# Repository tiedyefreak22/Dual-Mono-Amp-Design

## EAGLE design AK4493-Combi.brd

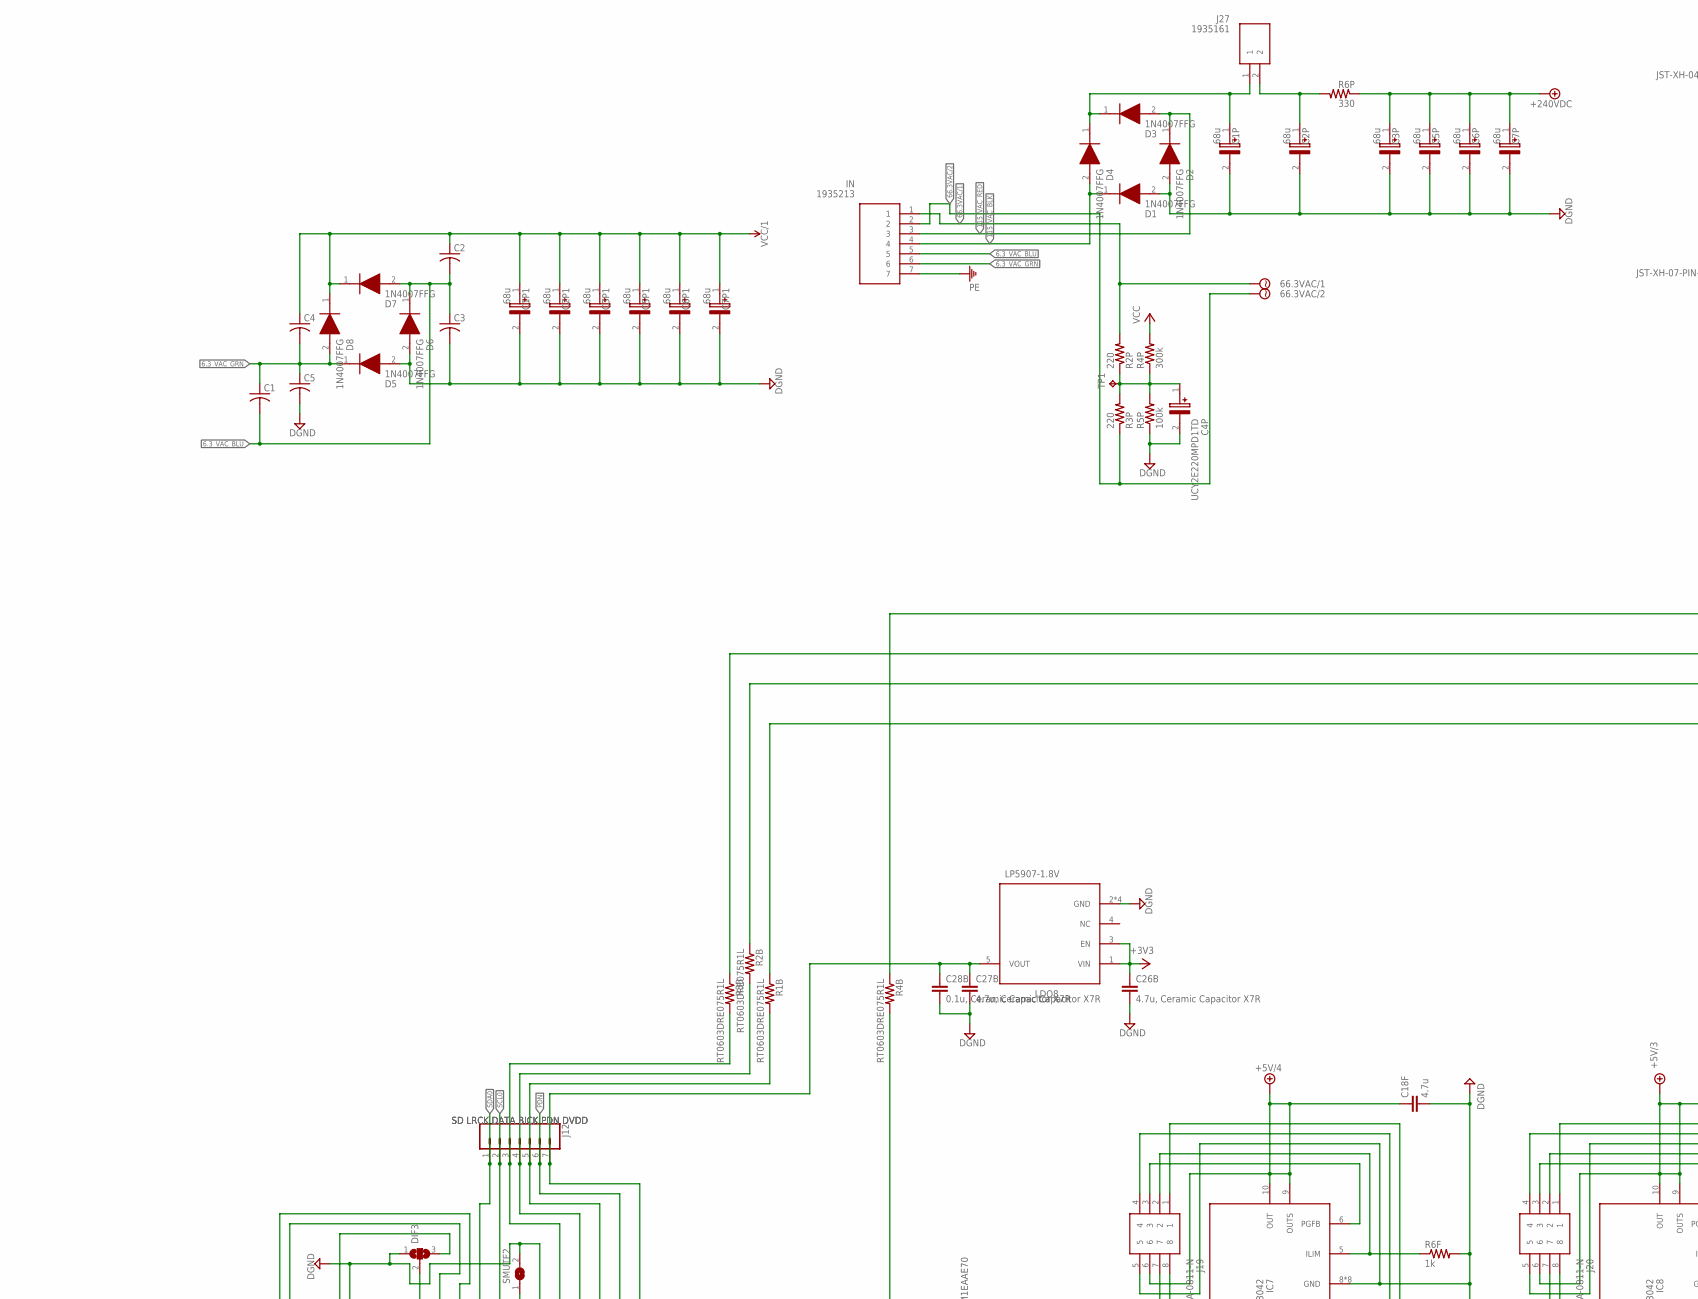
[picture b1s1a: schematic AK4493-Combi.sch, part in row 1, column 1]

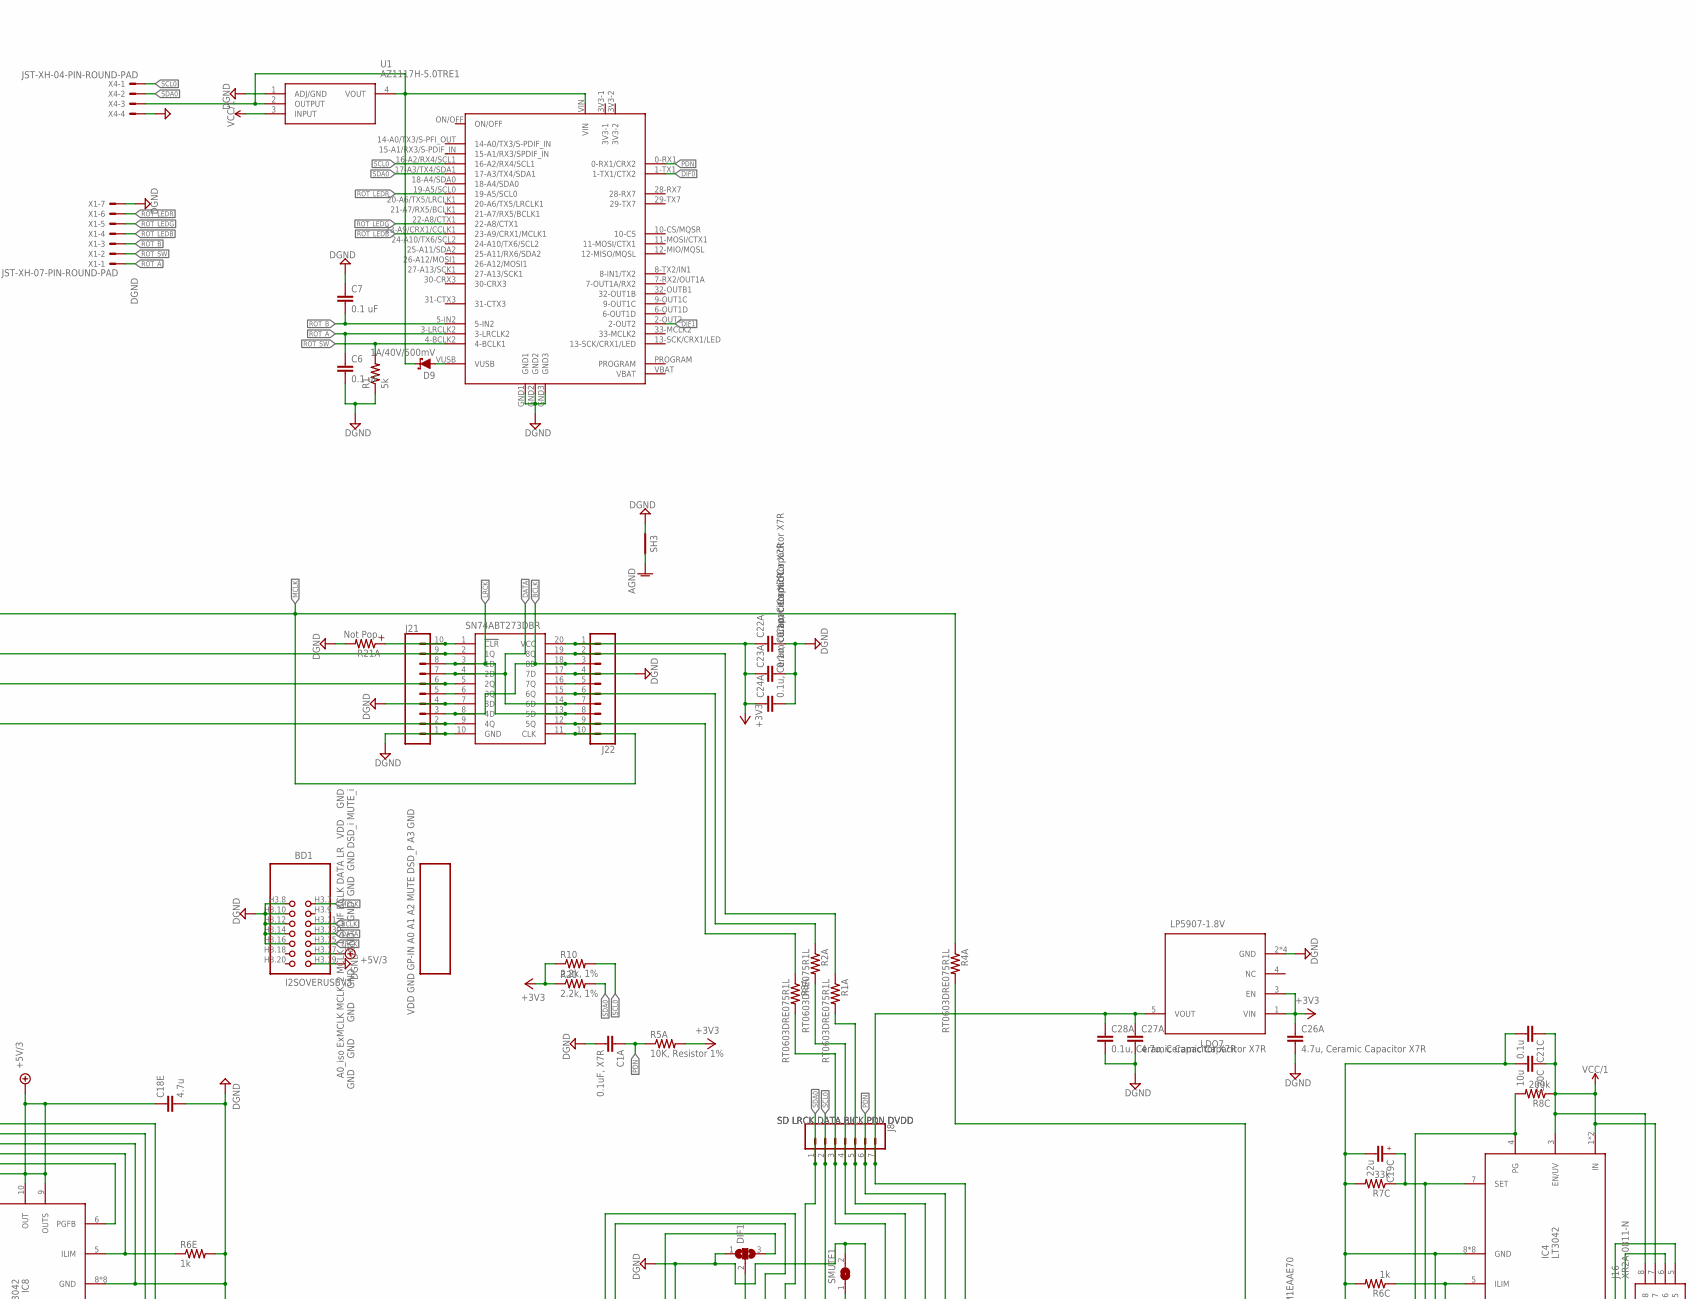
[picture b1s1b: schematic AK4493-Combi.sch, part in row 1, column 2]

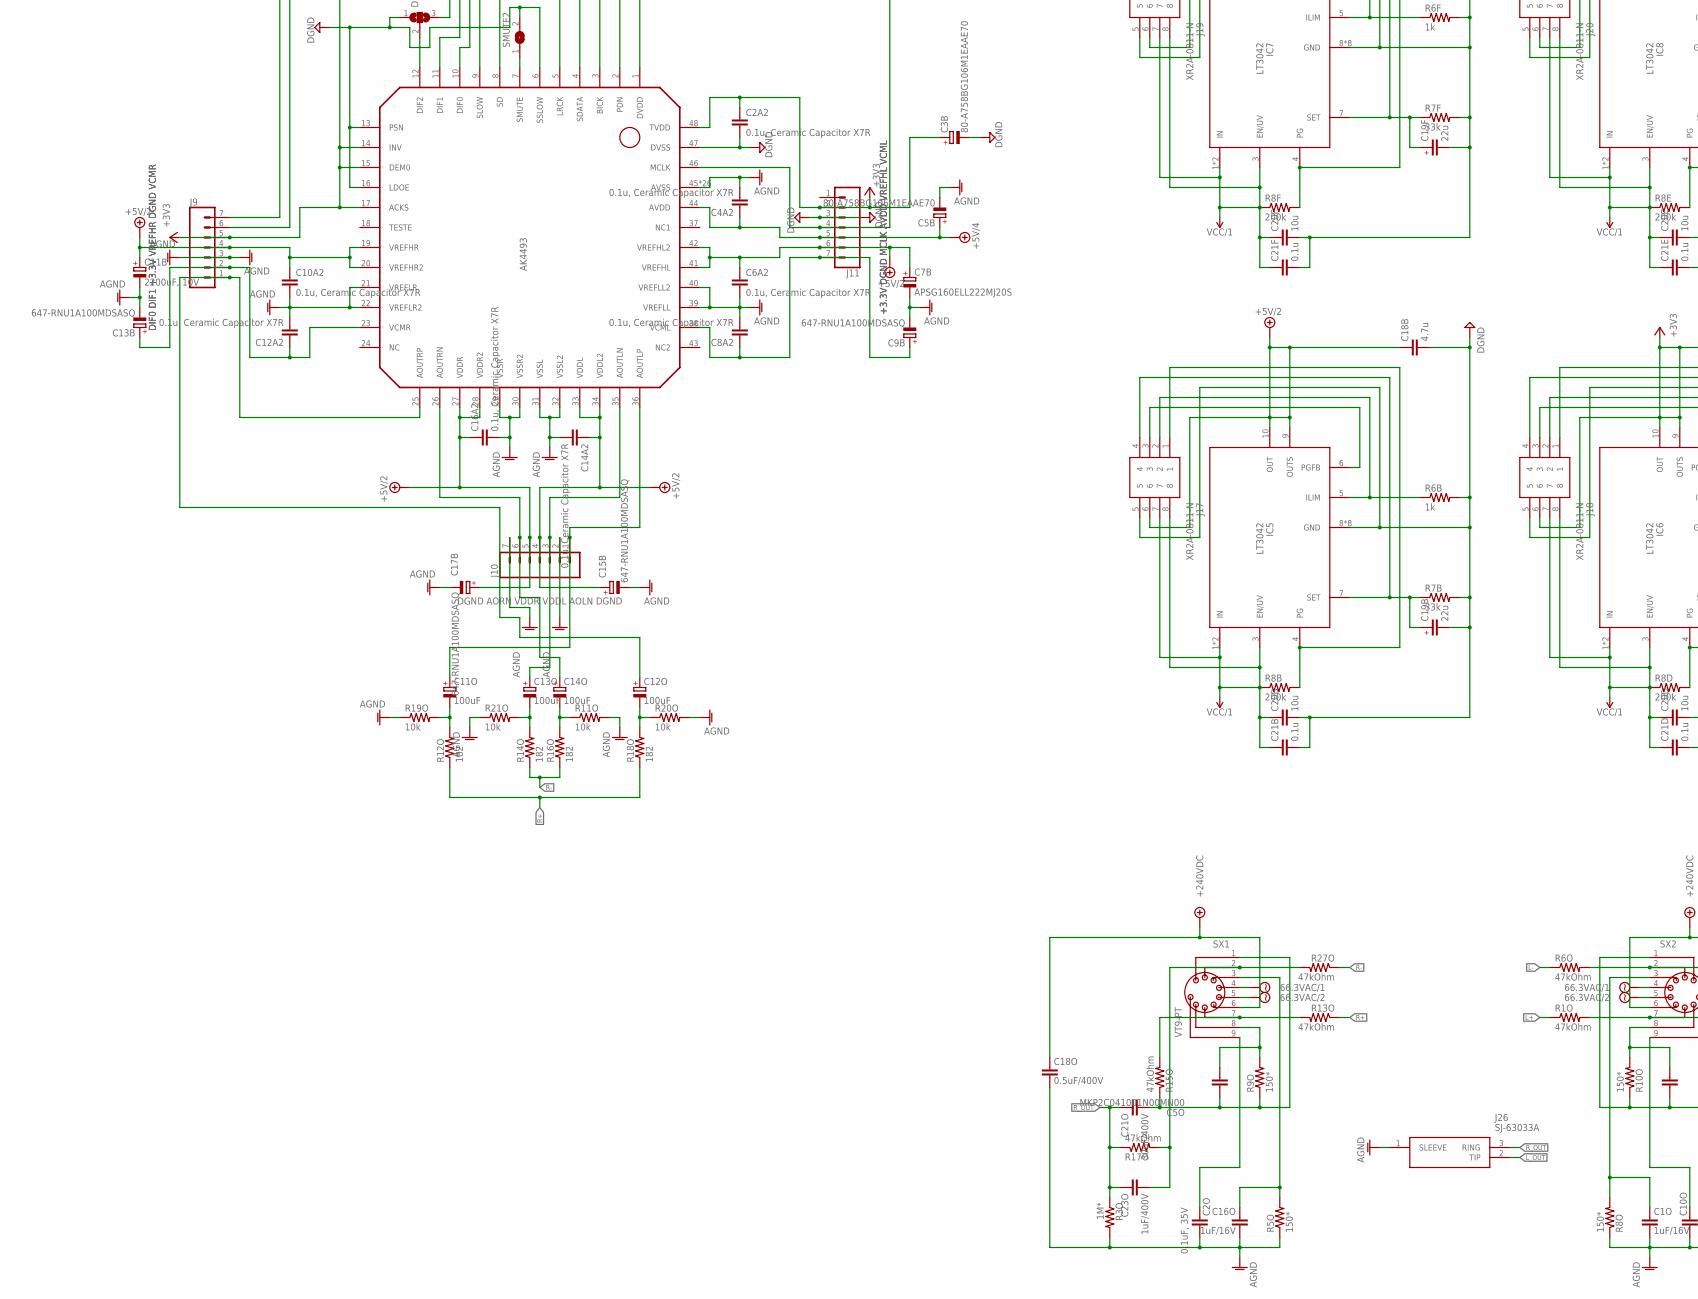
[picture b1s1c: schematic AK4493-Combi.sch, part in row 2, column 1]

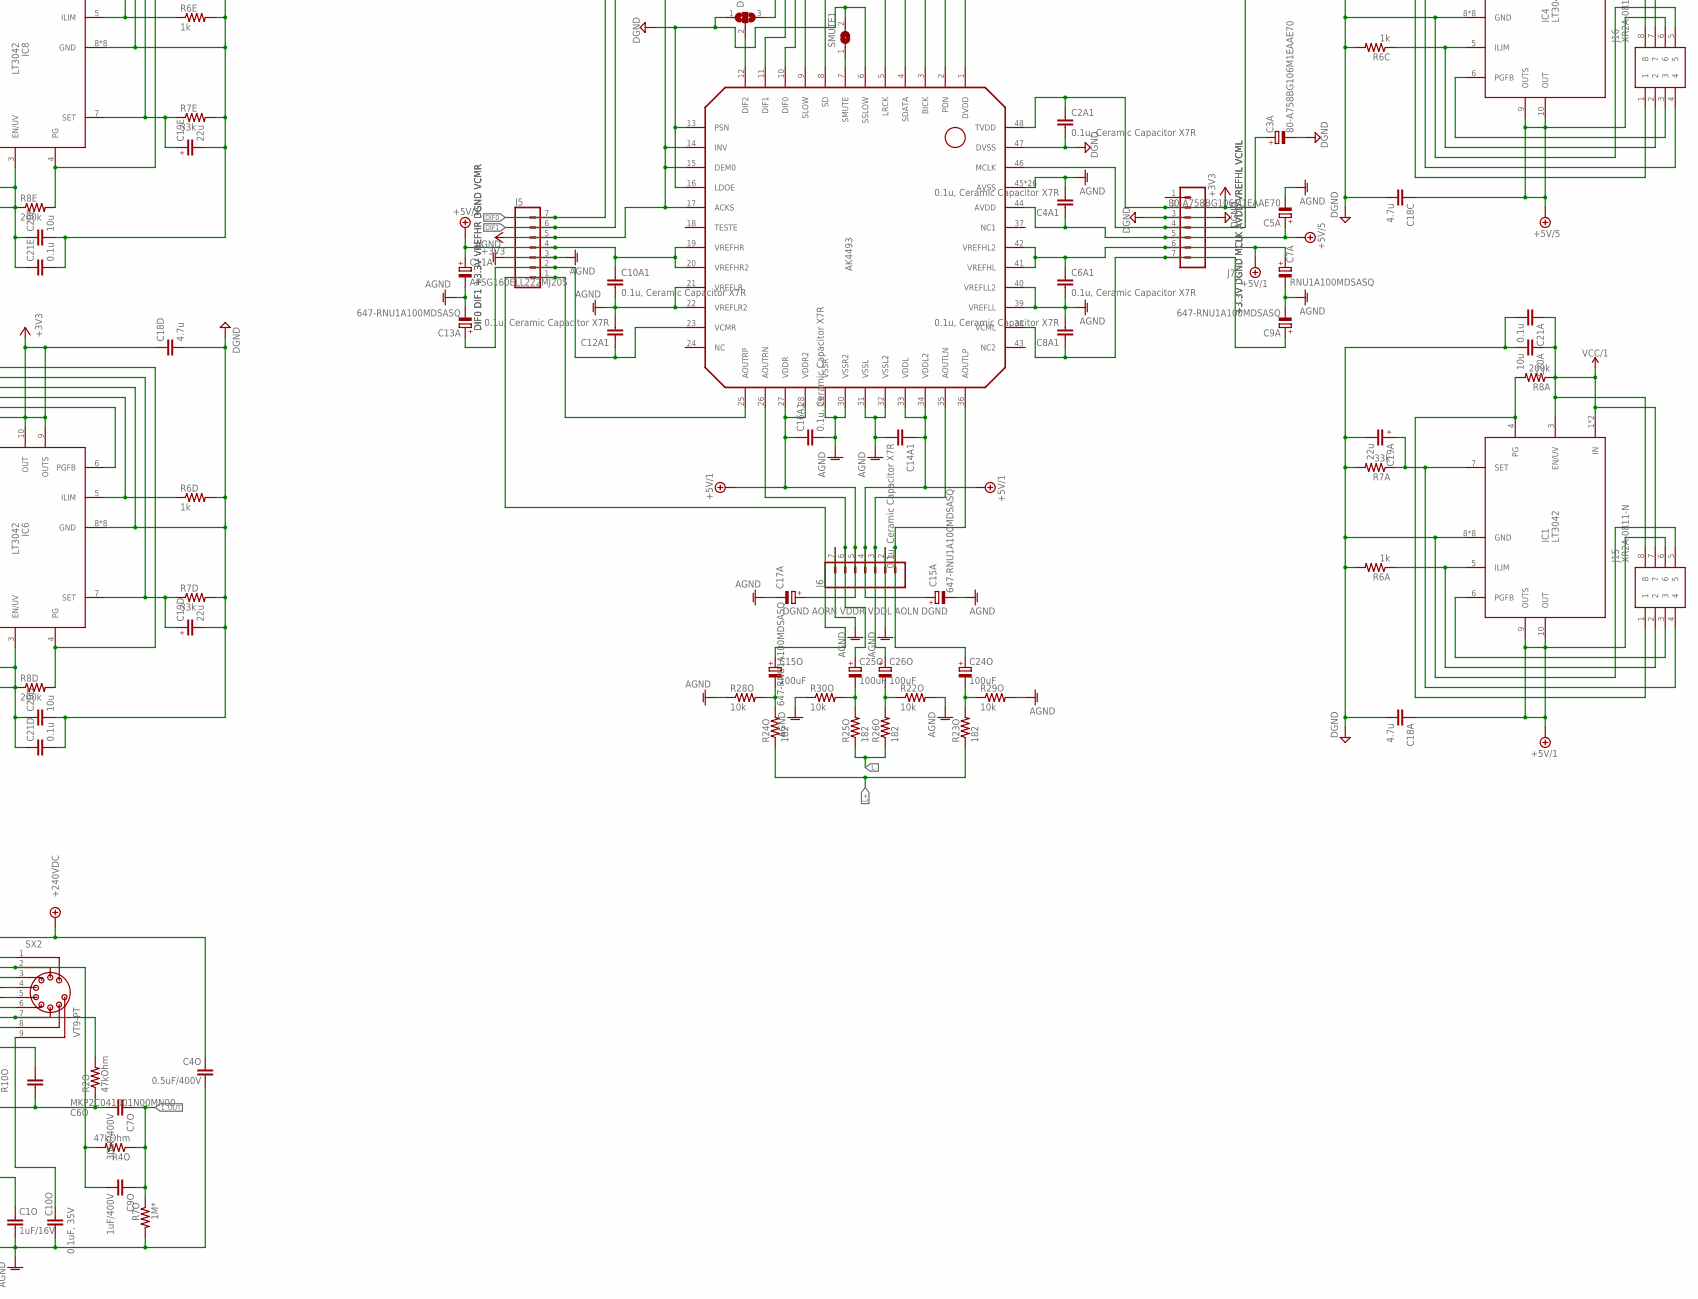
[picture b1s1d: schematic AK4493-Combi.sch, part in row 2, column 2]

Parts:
BD1: I2SOVERUSBV3
C1, C2, C3, C4, C5: C-US075-032X103; C075-032X103
C1A: 0.1uF, X7R; CAPC2012X135N
C1O, C16O: 1uF/16V; MKP2C041001N00MN00
C1P, C1P1, C2P, C2P1, C3P, C3P1, C5P, C5P1, C6P, C6P1, C7P, C7P1: 68u; CAPPRD750W80D1475H4700
C2A1, C2A2, C4A1, C4A2, C6A1, C6A2, C8A1, C8A2, C10A1, C10A2, C12A1, C12A2, C14A1, C14A2, C16A1, C16A2: 0.1u, Ceramic Capacitor X7R; CAPC1608X95N
C2O, C10O: 0.1uF, 35V; MKS4B031002A00JC00
C3A: 80-A758BG106M1EAAE70; CAPPRD150W45D450H600
C3B, C5A, C5B: 80-A758BG106M1EAAE70; CAPPRD200W55D500H800
C4O, C18O: 0.5uF/400V; MKP4G034705D00KSSD
C4P: UCY2E220MPD1TD; CAPPRD500W60D1025H1750
C5O, C6O: MKP2C041001N00MN00
C6, C7: 0.1 uF; C0603
C7A: RNU1A100MDSASQ; CAPPRD150W45D450H600
C7B, C11A: APSG160ELL222MJ20S; CAPPRD500W60D1025H2150
C7O, C21O: 30uF/400V; DCP4G053006ID2KSSD
C9A, C9B, C13A, C13B, C15A, C15B, C17A, C17B: 647-RNU1A100MDSASQ; CAPPRD150W45D450H600
C9O, C23O: 1uF/400V; MKP4G041005I00JSSD
C11B: 2200uF, 10V; CAPPRD500W60D1025H2150
C11O, C12O, C13O, C14O, C15O, C24O, C25O, C26O: 100uF; CAPPRD350W60D825H1300
C18A, C18B, C18C, C18D, C18E, C18F: 4.7u; CAPC2013X140N
C19A, C19B, C19C, C19D, C19E, C19F: 22u; C1206
C20A, C20B, C20C, C20D, C20E, C20F: 10u; CAPC2012X135N
C21A, C21B, C21C, C21D, C21E, C21F: 0.1u; CAPC2012X135N
C22A, C23A, C24A, C28A, C28B: 0.1u, Ceramic Capacitor X7R; CAPC2012X135N
C26A, C26B, C27A, C27B: 4.7u, Ceramic Capacitor X7R; CAPC2013X140N
D1, D2, D3, D4, D5, D6, D7, D8: 1N4007FFG; DIOAD1405W86L465D235
D9: 1A/40V/500mV; SMA-DIODE
DIF1, DIF3: SJ2W; SJ_2
IC1, IC4, IC5, IC6, IC7, IC8: LT3042; SOP50P490X110-11N
IC2, IC3: AK4493; LQFP48_
IC4A: SN74ABT273DBR; SOP65P780X200-20N
IN: 1935213
J5, J6, J7, J8, J9, J10, J11, J12: CONN_07; 1X07
J15, J16, J17, J18, J19, J20: XR2A-0811-N; DIPS762W51P254L1016H390Q8N
J21, J22: CONN_10"; 1X10
J26: SJ-63033A; SJ63033A
J27: 1935161
LDO7, LDO8: LP5907-1.8V; SOT95P280X145-5N
R1: 5k; R0603
R1A, R1B, R2A, R2B, R3A, R3B, R4A, R4B: RT0603DRE075R1L; RESC1608X55N
R1O, R2O, R4O, R6O, R13O, R15O, R17O, R27O: 47kOhm; RESAD1540W55L620D230
R2P, R3P: 220; 0411/15
R3O, R7O: 1M*; RESAD1540W60L620D230
R4P: 300k; 0411/15
R5A: 10K, Resistor 1%; RESC2012X50N
R5O, R8O, R9O, R10O: 150*; RESAD1540W55L620D230
R5P: 100k; 0411/15
R6A, R6B, R6C, R6D, R6E, R6F: 1k; RESC2012X60N
R6P: 330; 0411/15
R7A, R7B, R7C, R7D, R7E, R7F: 33k; R0805
R8A, R8B, R8C, R8D, R8E, R8F: 200k; R0805
R10, R20: 2.2k, 1%; RCS0805_E3
R11O, R19O, R20O, R21O, R22O, R28O, R29O, R30O: 10k; RESAD1540W55L620D230
R12O, R14O, R16O, R18O, R23O, R24O, R25O, R26O: 182; RESAD1590W60L630D240
R21A: Not Pop.; R0805-POL
SH3: SHORTA5; SHORT_ALL-50
SMUTE1, SMUTE2: SJ
SX1, SX2: VT9-PT
TP1: TPB2,54; B2,54
U1: AZ1117H-5.0TRE1; SOT230P700X180-4N
U$1: TEENSY40
X1: JST-XH-07-PIN-ROUND-PAD; JST-XH-07-PACKAGE-ROUND-PAD
X4: JST-XH-04-PIN-ROUND-PAD; JST-XH-04-PACKAGE-ROUND-PAD

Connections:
6.3_VAC_BLU: C1.2, C2.2, C3.1, D6.1 (K), D7.2 (A), IN.5
6.3_VAC_GRN: C1.1, C4.2, C5.1, D5.1 (K), D8.2 (A), IN.6
66.3VAC/1: IN.1, R2P.2, SX1.4, SX2.4
66.3VAC/2: IN.2, R3P.1, SX1.5, SX2.5
115_VAC_BLK: D1.1 (K), D4.2 (A), IN.4
115_VAC_RED: D2.1 (K), D3.2 (A), IN.3
+3V3: C2A1.1, C2A2.1, C3A.1 (+), C3B.1 (+), C18D.1, C22A.1, C23A.1, C24A.1, C26A.1, C26B.1, DIF1.3, DIF3.3, IC2.14 (INV), IC2.15 (DEM0), IC2.17 (ACKS), IC2.48 (TVDD), IC3.14 (INV), IC3.15 (DEM0), IC3.17 (ACKS), IC3.48 (TVDD), IC4A.20 (VCC), IC6.9 (OUTS), IC6.10 (OUT), J5.5, J7.2, J9.5, J11.2, J18.6, J22.1, LDO7.1 (VIN), LDO7.3 (EN), LDO8.1 (VIN), LDO8.3 (EN), R5A.2, R10.1, R20.1
+5V/1: C6A1.1, C7A.1 (+), C10A1.1, C11A.1 (+), C14A1.1, C15A.1 (+), C16A1.1, C17A.1 (+), C18A.1, IC1.9 (OUTS), IC1.10 (OUT), IC2.19 (VREFHR), IC2.20 (VREFHR2), IC2.27 (VDDR), IC2.28 (VDDR2), IC2.33 (VDDL), IC2.34 (VDDL2), IC2.41 (VREFHL), IC2.42 (VREFHL2), J5.4, J6.4, J6.5, J7.6, J15.6
+5V/2: C6A2.1, C7B.1 (+), C10A2.1, C11B.1 (+), C14A2.1, C15B.1 (+), C16A2.1, C17B.1 (+), C18B.1, IC3.19 (VREFHR), IC3.20 (VREFHR2), IC3.27 (VDDR), IC3.28 (VDDR2), IC3.33 (VDDL), IC3.34 (VDDL2), IC3.41 (VREFHL), IC3.42 (VREFHL2), IC5.9 (OUTS), IC5.10 (OUT), J9.4, J10.4, J10.5, J11.6, J17.6
+5V/3: BD1.H3.17, C18E.1, IC8.9 (OUTS), IC8.10 (OUT), J20.6
+5V/4: C4A2.1, C5B.1 (+), C18F.1, IC3.44 (AVDD), IC7.9 (OUTS), IC7.10 (OUT), J11.5, J19.6
+5V/5: C4A1.1, C5A.1 (+), C18C.1, IC2.44 (AVDD), IC4.9 (OUTS), IC4.10 (OUT), J7.5, J16.6
+240VDC: C3P.1 (+), C4O.1, C5P.1 (+), C6P.1 (+), C7P.1 (+), C18O.1, R6P.1, SX1.6, SX2.6
AGND: C1O.2, C2O.2, C4A1.2, C4A2.2, C4O.2, C5A.2 (-), C5B.2 (-), C6A1.2, C6A2.2, C7A.2 (-), C7B.2 (-), C8A1.2, C8A2.2, C9A.2 (-), C9B.2 (-), C10A1.2, C10A2.2, C10O.2, C11A.2 (-), C11B.2 (-), C12A1.2, C12A2.2, C13A.2 (-), C13B.2 (-), C14A1.2, C14A2.2, C15A.2 (-), C15B.2 (-), C16A1.2, C16A2.2, C16O.2, C17A.2 (-), C17B.2 (-), C18O.2, IC2.21 (VREFLR), IC2.22 (VREFLR2), IC2.29 (VSSR), IC2.30 (VSSR2), IC2.31 (VSSL), IC2.32 (VSSL2), IC2.39 (VREFLL), IC2.40 (VREFLL2), IC2.45 (AVSS), IC2.P$1 (AVSS), IC2.P$2 (AVSS), IC2.P$3 (AVSS), IC2.P$4 (AVSS), IC2.P$5 (AVSS), IC2.P$6 (AVSS), IC2.P$7 (AVSS), IC2.P$8 (AVSS), IC2.P$9 (AVSS), IC2.P$10 (AVSS), IC2.P$11 (AVSS), IC2.P$12 (AVSS), IC2.P$13 (AVSS), IC2.P$14 (AVSS), IC2.P$15 (AVSS), IC2.P$16 (AVSS), IC2.P$17 (AVSS), IC2.P$18 (AVSS), IC2.P$19 (AVSS), IC2.P$20 (AVSS), IC2.P$21 (AVSS), IC2.P$22 (AVSS), IC2.P$23 (AVSS), IC2.P$24 (AVSS), IC2.P$25 (AVSS), IC3.21 (VREFLR), IC3.22 (VREFLR2), IC3.29 (VSSR), IC3.30 (VSSR2), IC3.31 (VSSL), IC3.32 (VSSL2), IC3.39 (VREFLL), IC3.40 (VREFLL2), IC3.45 (AVSS), IC3.P$1 (AVSS), IC3.P$2 (AVSS), IC3.P$3 (AVSS), IC3.P$4 (AVSS), IC3.P$5 (AVSS), IC3.P$6 (AVSS), IC3.P$7 (AVSS), IC3.P$8 (AVSS), IC3.P$9 (AVSS), IC3.P$10 (AVSS), IC3.P$11 (AVSS), IC3.P$12 (AVSS), IC3.P$13 (AVSS), IC3.P$14 (AVSS), IC3.P$15 (AVSS), IC3.P$16 (AVSS), IC3.P$17 (AVSS), IC3.P$18 (AVSS), IC3.P$19 (AVSS), IC3.P$20 (AVSS), IC3.P$21 (AVSS), IC3.P$22 (AVSS), IC3.P$23 (AVSS), IC3.P$24 (AVSS), IC3.P$25 (AVSS), J5.3, J6.2, J6.7, J9.3, J10.2, J10.7, J26.1 (SLEEVE), R3O.2, R5O.1, R7O.2, R8O.1, R11O.2, R19O.1, R20O.2, R21O.1, R22O.2, R28O.1, R29O.2, R30O.1, SH3.2
BCLK: BD1.H3.11, IC4A.8 (4D), IC4A.18 (8D), J21.3, J22.3
DATA: BD1.H3.13, IC4A.4 (2D), IC4A.14 (6D), J21.7, J22.7
DGND: BD1.H3.8, BD1.H3.10, BD1.H3.12, BD1.H3.14, BD1.H3.16, BD1.H3.19, C1A.2, C1P.2 (-), C1P1.2 (-), C2A1.2, C2A2.2, C2P.2 (-), C2P1.2 (-), C3.2, C3A.2 (-), C3B.2 (-), C3P.2 (-), C3P1.2 (-), C4P.2 (-), C5.2, C5P.2 (-), C5P1.2 (-), C6.2, C6P.2 (-), C6P1.2 (-), C7.1, C7P.2 (-), C7P1.2 (-), C18A.2, C18B.2, C18C.2, C18D.2, C18E.2, C18F.2, C19A.2, C19A.DGND (2), C19B.2, C19B.DGND (2), C19C.2, C19C.DGND (2), C19D.2, C19D.DGND (2), C19E.2, C19E.DGND (2), C19F.2, C19F.DGND (2), C20A.2, C20B.2, C20C.2, C20D.2, C20E.2, C20F.2, C21A.2, C21B.2, C21C.2, C21D.2, C21E.2, C21F.2, C22A.2, C23A.2, C24A.2, C26A.2, C26B.2, C27A.2, C27B.2, C28A.2, C28B.2, D1.2 (A), D2.2 (A), D5.2 (A), D6.2 (A), DIF1.1, DIF3.1, IC1.8 (GND), IC1.11 (GND), IC1.P$1 (GND), IC1.P$2 (GND), IC1.P$3 (GND), IC1.P$4 (GND), IC1.P$5 (GND), IC1.P$6 (GND), IC2.6 (SSLOW), IC2.13 (PSN), IC2.16 (LDOE), IC2.47 (DVSS), IC3.6 (SSLOW), IC3.13 (PSN), IC3.16 (LDOE), IC3.47 (DVSS), IC4.8 (GND), IC4.11 (GND), IC4.P$1 (GND), IC4.P$2 (GND), IC4.P$3 (GND), IC4.P$4 (GND), IC4.P$5 (GND), IC4.P$6 (GND), IC4A.7 (3D), IC4A.10 (GND), IC4A.17 (7D), IC5.8 (GND), IC5.11 (GND), IC5.P$1 (GND), IC5.P$2 (GND), IC5.P$3 (GND), IC5.P$4 (GND), IC5.P$5 (GND), IC5.P$6 (GND), IC6.8 (GND), IC6.11 (GND), IC6.P$1 (GND), IC6.P$2 (GND), IC6.P$3 (GND), IC6.P$4 (GND), IC6.P$5 (GND), IC6.P$6 (GND), IC7.8 (GND), IC7.11 (GND), IC7.P$1 (GND), IC7.P$2 (GND), IC7.P$3 (GND), IC7.P$4 (GND), IC7.P$5 (GND), IC7.P$6 (GND), IC8.8 (GND), IC8.11 (GND), IC8.P$1 (GND), IC8.P$2 (GND), IC8.P$3 (GND), IC8.P$4 (GND), IC8.P$5 (GND), IC8.P$6 (GND), J7.3, J11.3, J15.5, J16.5, J17.5, J18.5, J19.5, J20.5, J21.1, J21.4, J22.4, LDO7.2 (GND), LDO7.DGND (GND), LDO7.DGND2 (GND), LDO7.DGND3 (GND), LDO8.2 (GND), LDO8.DGND (GND), LDO8.DGND2 (GND), LDO8.DGND3 (GND), R1.1, R5P.1, R6A.2, R6B.2, R6C.2, R6D.2, R6E.2, R6F.2, R7A.2, R7B.2, R7C.2, R7D.2, R7E.2, R7F.2, R21A.2, R21A.DGND (2), SH3.1, SMUTE1.2, SMUTE2.2, U1.1 (ADJ/GND), U$1.GND1, U$1.GND2, U$1.GND3, X1.7, X4.4
DIF0: IC2.10 (DIF0), J5.7, U$1.1-TX1 (1-TX1/CTX2)
DIF1: IC2.11 (DIF1), J5.6, U$1.2-OUT2
L+: R1O.1, R23O.1, R24O.1
L-: R6O.1, R25O.1, R26O.1
LRCK: BD1.H3.15, IC4A.3 (1D), IC4A.13 (5D), J21.8, J22.8
L_OUT: C7O.1, C9O.1, J26.2 (TIP), R4O.1, R7O.1
MCLK: BD1.H3.7, IC4A.11 (CLK), J22.10, R4A.1, R4B.1
unnamed: IC4A.1 (!CLR), J21.10, R21A.1
unnamed: C8A2.1, C9B.1 (+), IC3.38 (VCML), J11.7
unnamed: C5O.1, C21O.2, R9O.1, R15O.1, SX1.1
unnamed: IC4A.6 (3Q), J21.5
unnamed: IC4A.16 (7Q), J22.5
unnamed: C23O.2, R17O.2, R27O.2, SX1.2
unnamed: C16O.1, R5O.2, SX1.3
unnamed: C2O.1, SX1.9
unnamed: R1O.2, R2O.2, SX2.7
unnamed: C6O.1, C7O.2, R2O.1, R10O.1, SX2.1
unnamed: C9O.2, R4O.2, R6O.2, SX2.2
unnamed: C1O.1, R8O.2, SX2.3
unnamed: C10O.1, SX2.9
unnamed: C19A.1, IC1.7 (SET), J15.4, R7A.1
unnamed: D9.A, U$1.VUSB
unnamed: R13O.2, R15O.2, SX1.7
unnamed: IC5.4 (PG), J17.1, R8B.2
unnamed: IC5.6 (PGFB), J17.3
unnamed: IC2.5 (LRCK), J8.3, R3A.2
unnamed: IC2.4 (SDATA), J8.4, R2A.2
unnamed: IC2.3 (BICK), J8.5, R1A.2
unnamed: IC5.5 (ILIM), J17.2, R6B.1
unnamed: IC4A.19 (8Q), J22.2, R1A.1
unnamed: IC4A.15 (6Q), J22.6, R2A.1
unnamed: IC4A.12 (5Q), J22.9, R3A.1
unnamed: C25O.1 (+), IC2.26 (AOUTRN), J6.6
unnamed: IC3.3 (BICK), J12.5, R1B.2
unnamed: IC3.4 (SDATA), J12.4, R2B.2
unnamed: IC3.5 (LRCK), J12.3, R3B.2
unnamed: IC4A.9 (4Q), J21.2, R1B.1
unnamed: IC4A.5 (2Q), J21.6, R2B.1
unnamed: IC4A.2 (1Q), J21.9, R3B.1
unnamed: C11O.2 (-), R12O.2, R19O.2
unnamed: IC6.4 (PG), J18.1, R8D.2
unnamed: IC3.46 (MCLK), J11.4, R4B.2
unnamed: IC7.5 (ILIM), J19.2, R6F.1
unnamed: C27A.1, C28A.1, IC2.1 (DVDD), J8.7, LDO7.5 (VOUT)
unnamed: IC6.6 (PGFB), J18.3
unnamed: D9.C, U1.2 (OUTPUT), U1.4 (VOUT), U$1.VIN, X4.3
unnamed: IC6.5 (ILIM), J18.2, R6D.1
unnamed: IC1.6 (PGFB), J15.3
unnamed: C19D.1, IC6.7 (SET), J18.4, R7D.1
unnamed: IC7.4 (PG), J19.1, R8F.2
unnamed: C12O.2 (-), R18O.2, R20O.1
unnamed: C19F.1, IC7.7 (SET), J19.4, R7F.1
unnamed: IC8.4 (PG), J20.1, R8E.2
unnamed: C14O.2 (-), R11O.1, R16O.2
unnamed: C13O.2 (-), R14O.2, R21O.2
unnamed: IC8.6 (PGFB), J20.3
unnamed: IC8.5 (ILIM), J20.2, R6E.1
unnamed: C19E.1, IC8.7 (SET), J20.4, R7E.1
unnamed: C15O.2 (-), R24O.2, R28O.2
unnamed: C24O.2 (-), R23O.2, R29O.1
unnamed: C26O.2 (-), R22O.1, R26O.2
unnamed: C25O.2 (-), R25O.2, R30O.2
unnamed: C5O.2, R9O.2, SX1.8
unnamed: C6O.2, R10O.2, SX2.8
unnamed: C1P.1 (+), D3.1 (K), D4.1 (K), J27.1
unnamed: C2P.1 (+), J27.2, R6P.2
unnamed: C27B.1, C28B.1, IC3.1 (DVDD), J12.7, LDO8.5 (VOUT)
unnamed: C4P.1 (+), R2P.1, R3P.2, R4P.1, R5P.2, TP1.TP
unnamed: C12A1.1, C13A.1 (+), IC2.23 (VCMR), J5.2
unnamed: C11O.1 (+), IC3.36 (AOUTLP), J10.1
unnamed: C12O.1 (+), IC3.25 (AOUTRP), J9.1
unnamed: IC3.10 (DIF0), J9.7
unnamed: C24O.1 (+), IC2.36 (AOUTLP), J6.1
unnamed: C26O.1 (+), IC2.35 (AOUTLN), J6.3
unnamed: C13O.1 (+), IC3.35 (AOUTLN), J10.3
unnamed: C14O.1 (+), IC3.26 (AOUTRN), J10.6
unnamed: C15O.1 (+), IC2.25 (AOUTRP), J5.1
unnamed: IC2.46 (MCLK), J7.4, R4A.2
unnamed: C12A2.1, C13B.1 (+), IC3.23 (VCMR), J9.2
unnamed: C8A1.1, C9A.1 (+), IC2.38 (VCML), J7.7
unnamed: C19B.1, IC5.7 (SET), J17.4, R7B.1
unnamed: IC1.4 (PG), J15.1, R8A.2
unnamed: DIF1.2, IC2.12 (DIF2)
unnamed: IC2.7 (SMUTE), SMUTE1.1
unnamed: DIF3.2, IC3.12 (DIF2)
unnamed: C19C.1, IC4.7 (SET), J16.4, R7C.1
unnamed: IC4.6 (PGFB), J16.3
unnamed: IC4.5 (ILIM), J16.2, R6C.1
unnamed: IC1.5 (ILIM), J15.2, R6A.1
unnamed: IC7.6 (PGFB), J19.3
unnamed: IC4.4 (PG), J16.1, R8C.2
unnamed: IC3.7 (SMUTE), SMUTE2.1
unnamed: IC3.11 (DIF1), J9.6
PDN: C1A.1, IC2.2 (PDN), IC3.2 (PDN), J8.6, J12.6, R5A.1, U$1.0-RX1 (0-RX1/CRX2)
PE: IN.7
R+: R12O.1, R13O.1, R18O.1
R-: R14O.1, R16O.1, R27O.1
ROT_A: C6.1, U$1.3-LRCLK2, X1.1
ROT_B: C7.2, U$1.5-IN2, X1.3
ROT_LEDB: U$1.23-A9/CRX1/CCLK1 (23-A9/CRX1/MCLK1), X1.4
ROT_LEDG: U$1.22-A8/CTX1, X1.5
ROT_LEDR: U$1.19-A5/SCL0, X1.6
ROT_SW: R1.2, U$1.4-BCLK2 (4-BCLK1), X1.2
R_OUT: C21O.1, C23O.1, J26.3 (RING), R3O.1, R17O.1
SCL0: IC2.8 (SD), IC3.8 (SD), J8.2, J12.2, R10.2, U$1.16-A2/RX4/SCL1, X4.1
SDA0: IC2.9 (SLOW), IC3.9 (SLOW), J8.1, J12.1, R20.2, U$1.17-A3/TX4/SDA1, X4.2
VCC: R4P.2
VCC/1: C1P1.1 (+), C2.1, C2P1.1 (+), C3P1.1 (+), C4.1, C5P1.1 (+), C6P1.1 (+), C7P1.1 (+), C20A.1, C20B.1, C20C.1, C20D.1, C20E.1, C20F.1, C21A.1, C21B.1, C21C.1, C21D.1, C21E.1, C21F.1, D7.1 (K), D8.1 (K), IC1.1 (IN), IC1.2 (IN), IC1.3 (EN/UV), IC4.1 (IN), IC4.2 (IN), IC4.3 (EN/UV), IC5.1 (IN), IC5.2 (IN), IC5.3 (EN/UV), IC6.1 (IN), IC6.2 (IN), IC6.3 (EN/UV), IC7.1 (IN), IC7.2 (IN), IC7.3 (EN/UV), IC8.1 (IN), IC8.2 (IN), IC8.3 (EN/UV), J15.7, J15.8, J16.7, J16.8, J17.7, J17.8, J18.7, J18.8, J19.7, J19.8, J20.7, J20.8, R8A.1, R8B.1, R8C.1, R8D.1, R8E.1, R8F.1, U1.3 (INPUT)

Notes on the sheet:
+3.3V DGND MCLK AVDD VREFHL VCML
DIF0 DIF1 +3.3V VREFHR DGND VCMR
SD LRCK DATA BICK PDN DVDD
DGND AORN VDDR VDDL AOLN DGND

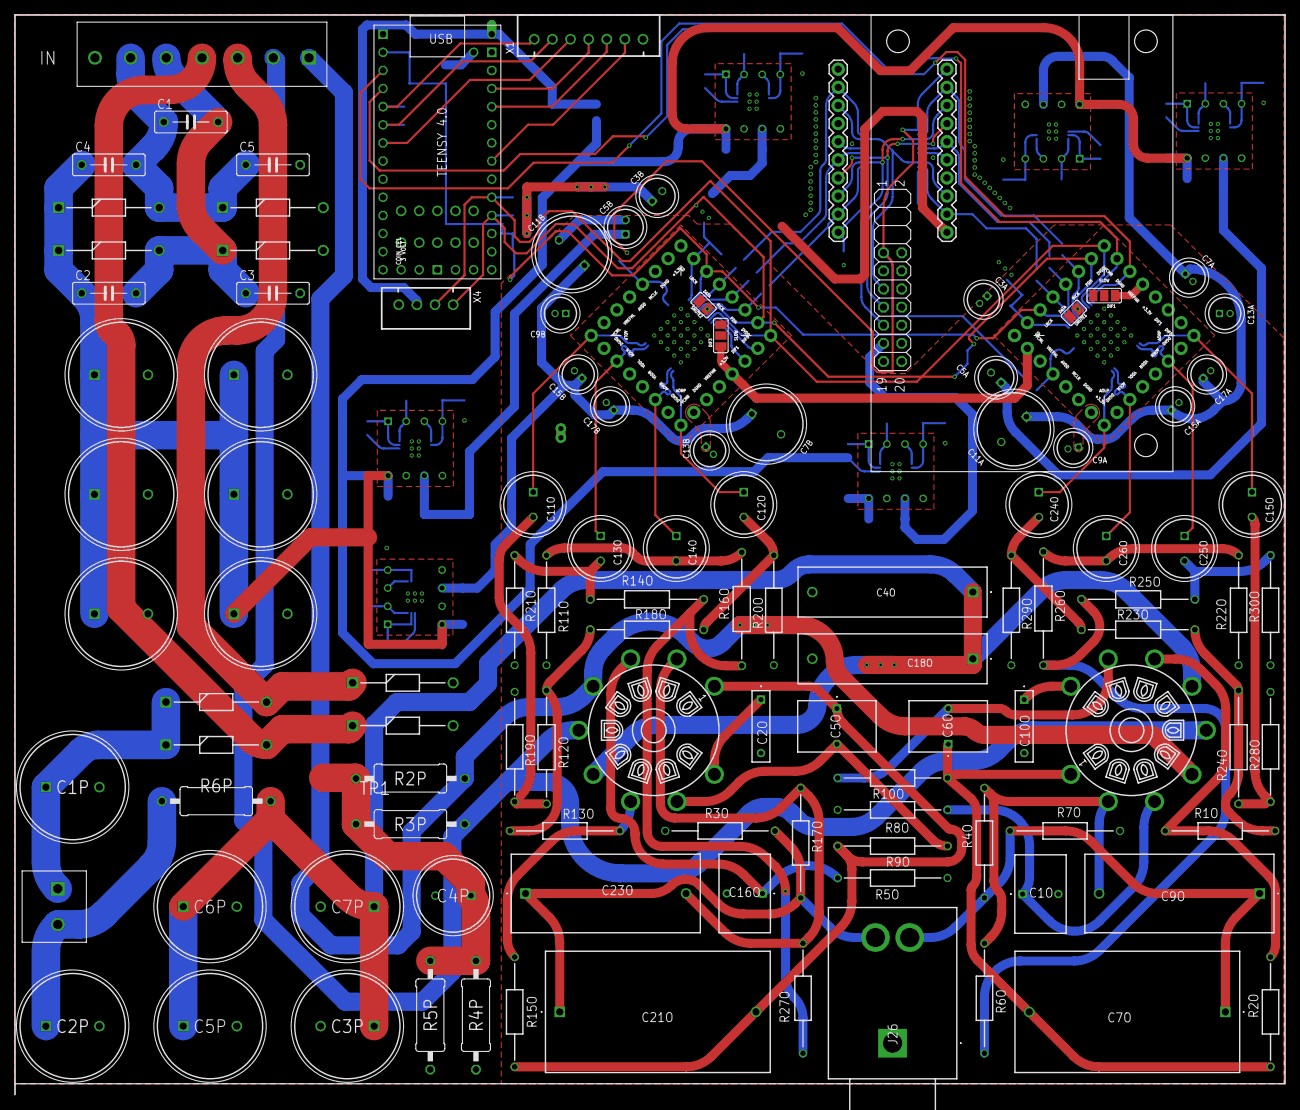
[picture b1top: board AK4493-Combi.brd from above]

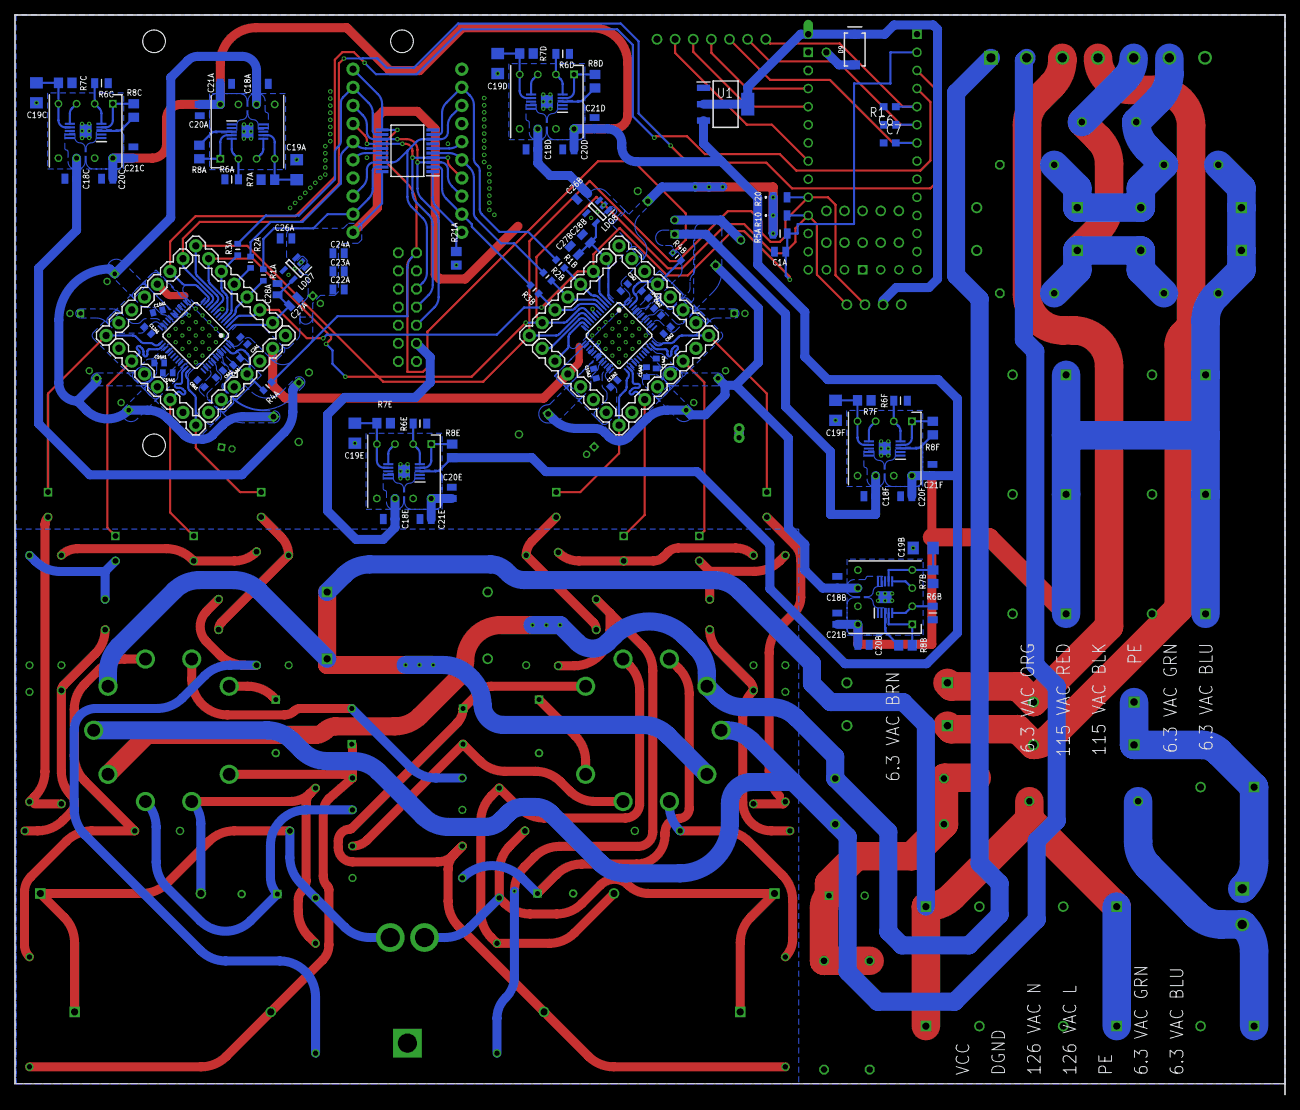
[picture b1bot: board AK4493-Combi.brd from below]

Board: 2 copper layers, 178.0 x 151.3 mm, 224 parts (110 on the bottom side), 123 nets.

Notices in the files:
parts and their libraries:
SparkFun-Connectors: Licensing: Creative Commons ShareAlike 4.0 International - https://creativecommons.org/licenses/by-sa/4.0
